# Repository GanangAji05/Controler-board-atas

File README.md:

# Controler-board-atas
controller board terdapat Stm32 sebagai MCU pengontrol komponen lainnya

Desain PCB

Desain 3D

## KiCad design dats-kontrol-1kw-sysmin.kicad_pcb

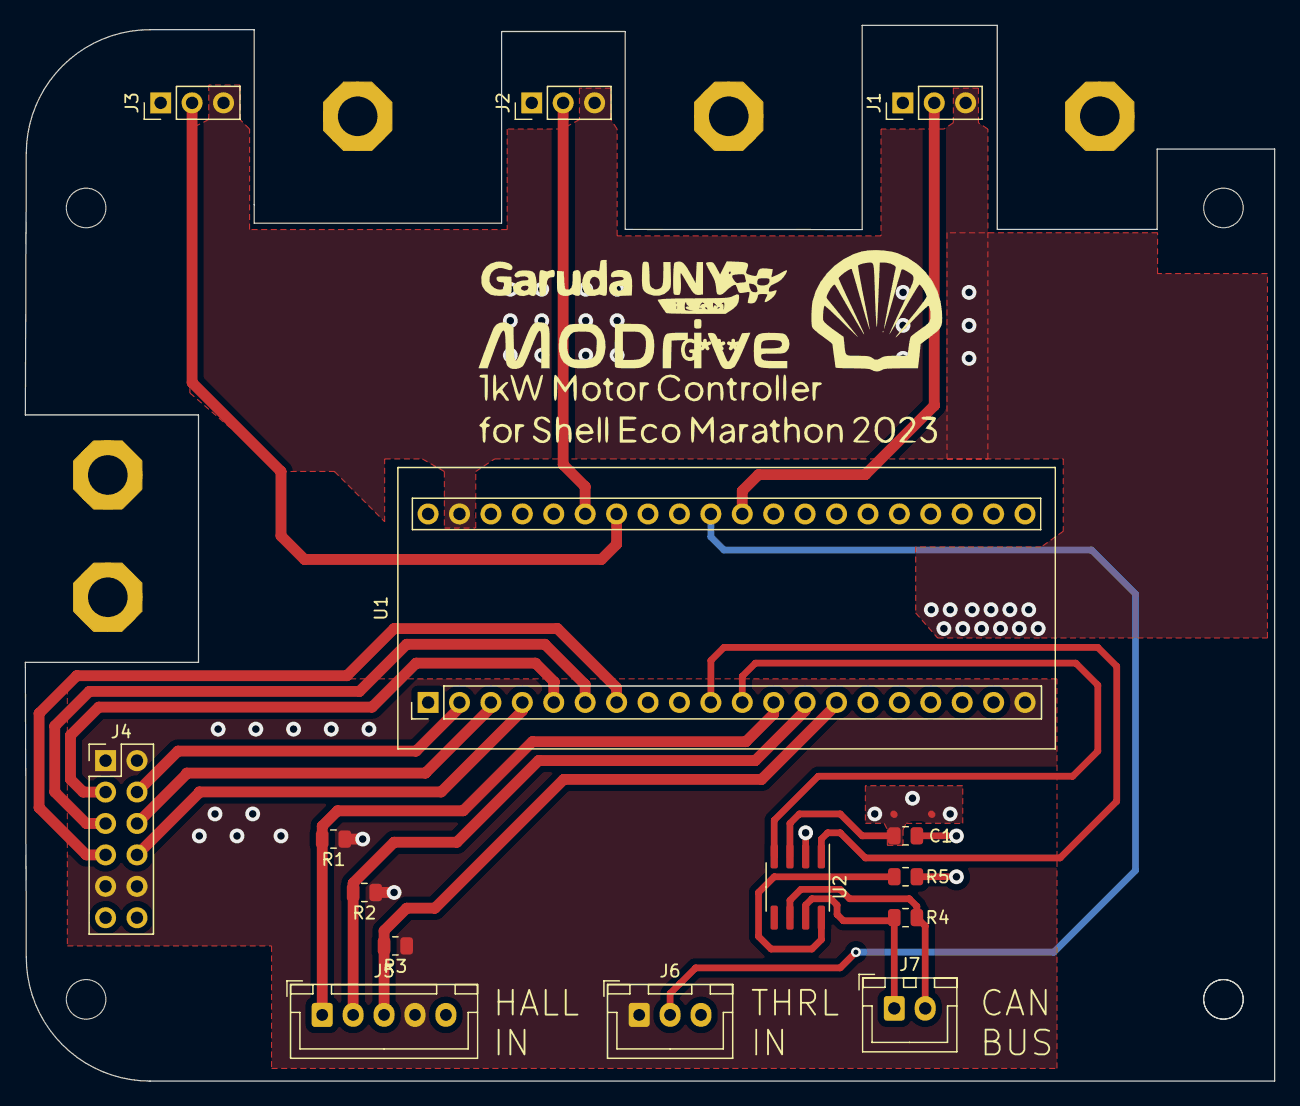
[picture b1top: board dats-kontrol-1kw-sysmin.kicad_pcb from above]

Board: 2 copper layers, 101.0 x 85.3 mm, 15 parts (0 on the bottom side), 21 nets.

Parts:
C1: C; R_0805_2012Metric
J1, J2, J3: Conn_01x03; PinHeader_1x03_P2.54mm_Vertical
J4: Conn_01x12; PinHeader_2x06_P2.54mm_Vertical
J5: Conn_01x05; JST_XH_B5B-XH-A_1x05_P2.50mm_Vertical
J6: Conn_01x03; JST_XH_B3B-XH-A_1x03_P2.50mm_Vertical
J7: Conn_01x02; JST_XH_B2B-XH-A_1x02_P2.50mm_Vertical
R1, R2, R3: 10K; R_0805_2012Metric
R4: 1K; R_0805_2012Metric
R5: 120; R_0805_2012Metric
U1: YAAJ_WeAct_BlackPill_Part_Like_SWD_Breakout; YAAJ_WeAct_BlackPill_2
U2: MCP2551-I-SN; SOIC-8_3.9x4.9mm_P1.27mm

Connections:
+3V3: J1.1, J2.1, J3.1, J4.1, J4.2, J4.9, J4.10, J5.4, J6.1, R1.1, R2.1, R3.1, U1.20 (3V3), U1.38 (3V3)
+5V: C1.1, U1.40 (5V), U2.3 (VDD)
A_H: J4.3, U1.5 (PA8)
A_L: J4.4, U1.2 (PB13)
B_H: J4.5, U1.6 (PA9)
B_L: J4.6, U1.3 (PB14)
CAN_RX: U1.11 (PB3), U2.4 (RXD)
CAN_TX: U1.10 (PA15), U2.1 (TXD)
CURRENT_SENS_A: J3.2, U1.34 (PB0)
CURRENT_SENS_B: J2.2, U1.35 (PB1)
CURRENT_SENS_C: J1.2, U1.30 (PA4)
C_H: J4.7, U1.7 (PA10)
C_L: J4.8, U1.4 (PB15)
GND: C1.2, J1.3, J2.3, J3.3, J4.11, J4.12, J5.5, J6.3, R4.1, U1.19 (GND), U1.39 (GND), U2.2 (VSS)
HALL_A: J5.1, R1.2, U1.12 (PB4)
HALL_B: J5.2, R2.2, U1.13 (PB5)
HALL_C: J5.3, R3.2, U1.14 (PB6)
unnamed: J7.1, R5.1, U2.7 (CANH)
unnamed: J7.2, R5.2, U2.6 (CANL)
unnamed: R4.2, U2.8 (Rs)
THROTTLE: J6.2, U1.31 (PA5)

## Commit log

2023-05-09 First init
2023-05-16 new layout
2023-05-16 adding stm32 symbol+footprint
2023-05-17 Layout STM
2023-05-19 adding some background
2023-11-20 commit 1
